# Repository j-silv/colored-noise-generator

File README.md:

# Colored Noise Generator
A white, pink, and brown noise analog signal generator.

# Schematic

# PCB

A single-layer board, DIY-fabricated at my university. Process included copper etching in vertical iron chloride (FeCl3) bath with manual agitation. Adhered to design rules (minimum trace widths, clearances, etc.) as specified by the fabrication technique.

# Simulation
*Coming soon...*

# Results
*Coming soon...*

# Acknowledgements
- Design inspired by [Rod Eliott's pink noise generator](https://sound-au.com/project11.htm)
- Thank you to Denis Muller at the [Physics and Engineering Faculty at the University of Strasbourg](https://physique-ingenierie.unistra.fr/) for helping me fabricate this board

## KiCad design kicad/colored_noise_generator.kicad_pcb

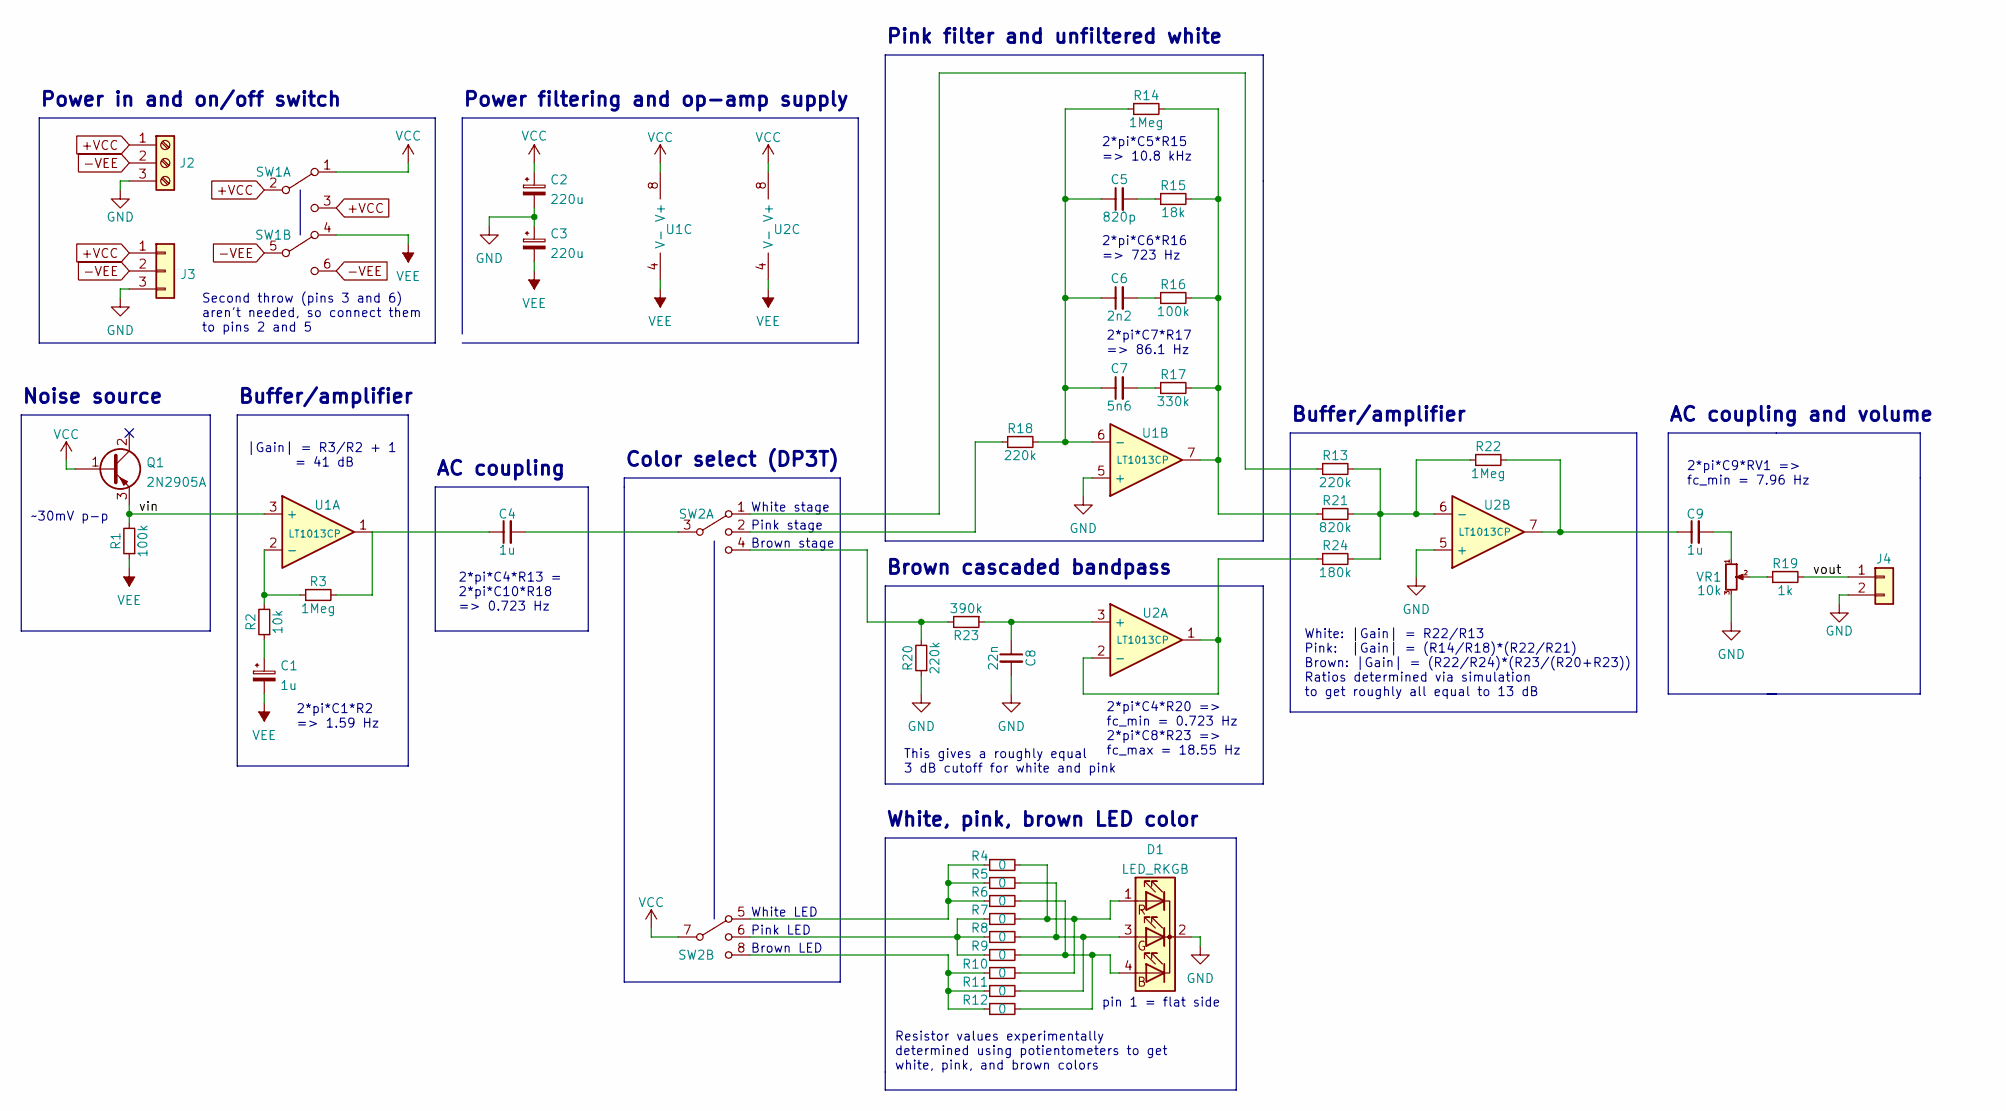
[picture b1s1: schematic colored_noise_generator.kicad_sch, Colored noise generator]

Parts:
C1: 1u; CP_Axial_L10.0mm_D6.0mm_P15.00mm_Horizontal
C2, C3: 220u; CP_Axial_L18.0mm_D8.0mm_P25.00mm_Horizontal
C4, C9: 1u; C_Rect_L7.0mm_W6.0mm_P5.00mm
C5: 820p; C_Disc_D4.7mm_W2.5mm_P5.00mm
C6: 2n2; C_Rect_L7.2mm_W2.5mm_P5.00mm_FKS2_FKP2_MKS2_MKP2
C7: 5n6; C_Rect_L7.2mm_W2.5mm_P5.00mm_FKS2_FKP2_MKS2_MKP2
C8: 22n; C_Rect_L7.2mm_W2.5mm_P5.00mm_FKS2_FKP2_MKS2_MKP2
D1: LED_RKGB; LED_D5.0mm-4_RGB
J2: Screw_Terminal_01x03; screw_terminal_1x3
J3: Conn_01x03; PinHeader_1x03_P2.54mm_Vertical
J4: Conn_01x02; PinHeader_1x02_P2.54mm_Vertical
Q1: 2N2905A; 2N2905A-TO-39
R1, R16: 100k; R_Axial_DIN0207_L6.3mm_D2.5mm_P7.62mm_Horizontal
R2: 10k; R_Axial_DIN0207_L6.3mm_D2.5mm_P7.62mm_Horizontal
R3, R14, R22: 1Meg; R_Axial_DIN0207_L6.3mm_D2.5mm_P7.62mm_Horizontal
R4, R5, R6, R7, R8, R9, R10, R11, R12: 0; R_Axial_DIN0207_L6.3mm_D2.5mm_P7.62mm_Horizontal
R13, R18, R20: 220k; R_Axial_DIN0207_L6.3mm_D2.5mm_P7.62mm_Horizontal
R15: 18k; R_Axial_DIN0207_L6.3mm_D2.5mm_P7.62mm_Horizontal
R17: 330k; R_Axial_DIN0207_L6.3mm_D2.5mm_P7.62mm_Horizontal
R19: 1k; R_Axial_DIN0207_L6.3mm_D2.5mm_P7.62mm_Horizontal
R21: 820k; R_Axial_DIN0207_L6.3mm_D2.5mm_P7.62mm_Horizontal
R23: 390k; R_Axial_DIN0207_L6.3mm_D2.5mm_P7.62mm_Horizontal
R24: 180k; R_Axial_DIN0207_L6.3mm_D2.5mm_P7.62mm_Horizontal
SW1: DPDT; dpdt
SW2: DP3T; dp3t
U1, U2: LT1013CP; DIP-8_W7.62mm_Socket
VR1: 10k; elegoo_pot

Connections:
+VCC: J2.1, J3.1, SW1.2 (B), SW1.3 (C)
-VEE: J2.2, J3.2, SW1.5 (B), SW1.6 (C)
/vin: Q1.3 (E), R1.2, U1.3 (+)
/vout: J4.1, R19.2
GND: C2.2, C3.1, C8.2, D1.2 (K), J2.3, J3.3, J4.2, R20.1, U1.5 (+), U2.5 (+), VR1.3
unnamed: C1.1, R2.1
unnamed: C4.1, R3.2, U1.1
unnamed: C4.2, SW2.3
unnamed: C5.1, C6.1, C7.1, R14.1, R18.2, U1.6 (-)
unnamed: C5.2, R15.1
unnamed: C6.2, R16.1
unnamed: C7.2, R17.1
unnamed: C8.1, R23.1, U2.3 (+)
unnamed: C9.1, R22.2, U2.7
unnamed: C9.2, VR1.1
unnamed: D1.1 (RA), R4.2, R7.2, R10.2
unnamed: D1.3 (GA), R5.2, R8.2, R11.2
unnamed: D1.4 (BA), R6.2, R9.2, R12.2
unnamed: R2.2, R3.1, U1.2 (-)
unnamed: R4.1, R5.1, R6.1, SW2.5
unnamed: R7.1, R8.1, R9.1, SW2.6
unnamed: R10.1, R11.1, R12.1, SW2.8
unnamed: R13.1, SW2.1
unnamed: R13.2, R21.2, R22.1, R24.2, U2.6 (-)
unnamed: R14.2, R15.2, R16.2, R17.2, R21.1, U1.7
unnamed: R18.1, SW2.2
unnamed: R19.1, VR1.2
unnamed: R20.2, R23.2, SW2.4
unnamed: R24.1, U2.1, U2.2 (-)
VCC: C2.1, Q1.1 (B), SW1.1 (A), SW2.7, U1.8 (V+), U2.8 (V+)
VEE: C1.2, C3.2, R1.1, SW1.4 (A), U1.4 (V-), U2.4 (V-)

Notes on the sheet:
Color select (DP3T)
~30mV p-p
2*pi*C4*R20 => fc_min = 0.723 Hz 2*pi*C8*R23 => fc_max = 18.55 Hz
Resistor values experimentally determined using potientometers to get white, pink, and brown colors
pin 1 = flat side
White, pink, brown LED color
Power in and on/off switch
Buffer/amplifier
Brown LED
2*pi*C6*R16 => 723 Hz
2*pi*C9*RV1 => fc_min = 7.96 Hz
Noise source
Pink filter and unfiltered white
Pink LED
|Gain| = R3/R2 + 1 = 41 dB
2*pi*C5*R15 => 10.8 kHz
2*pi*C7*R17 => 86.1 Hz
Pink stage
2*pi*C1*R2 => 1.59 Hz
2*pi*C4*R13 = 2*pi*C10*R18 => 0.723 Hz
White LED
Brown stage
Second throw (pins 3 and 6) aren't needed, so connect them to pins 2 and 5
White stage
White: |Gain| = R22/R13 Pink: |Gain| = (R14/R18)*(R22/R21) Brown: |Gain| = (R22/R24)*(R23/(R20+R23)) Ratios determined via simulation to get roughly all equal to 13 dB
Brown cascaded bandpass
AC coupling and volume
Power filtering and op-amp supply
AC coupling
This gives a roughly equal 3 dB cutoff for white and pink

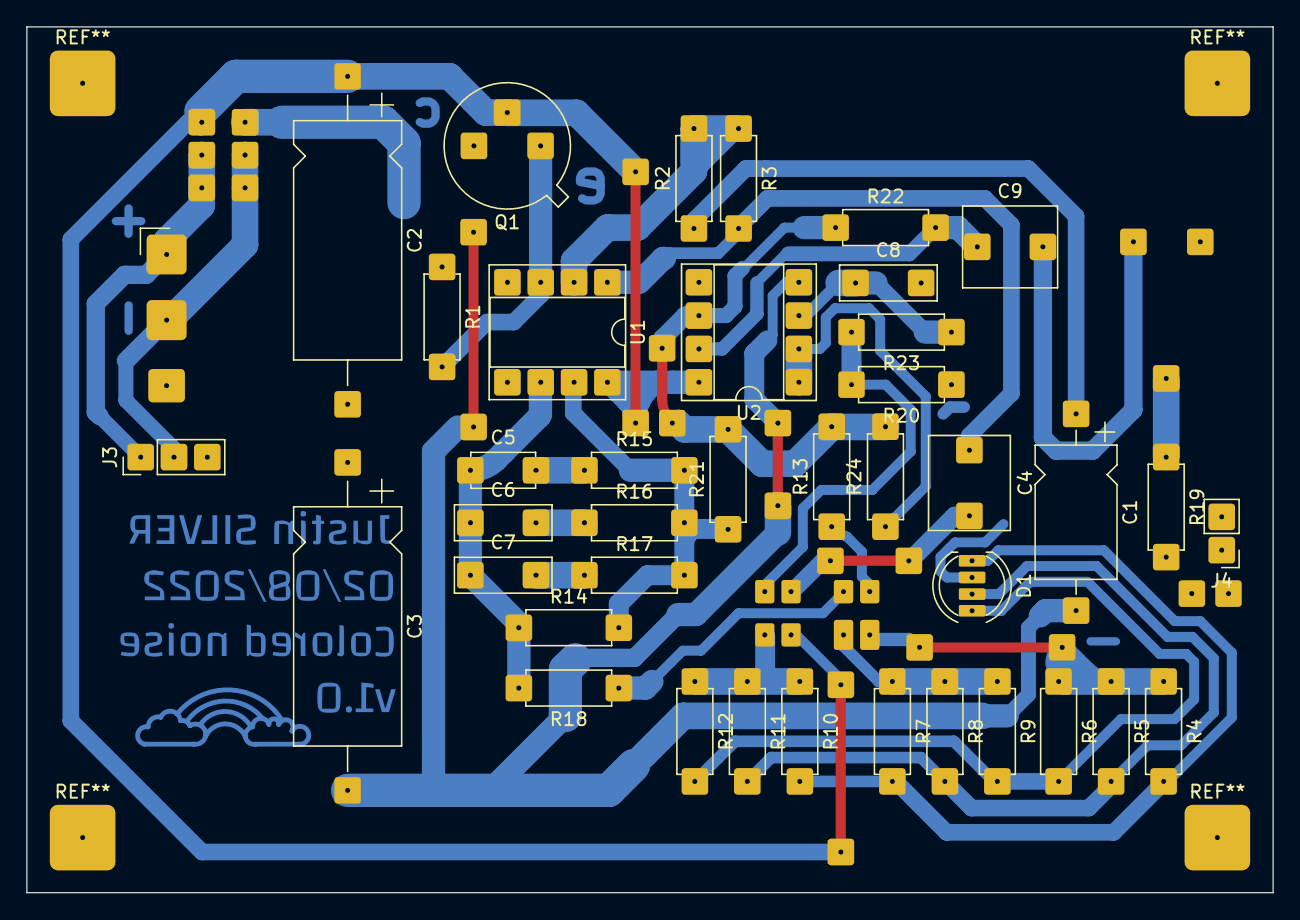
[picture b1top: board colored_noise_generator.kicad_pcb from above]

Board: 2 copper layers, 95.0 x 66.0 mm, 43 parts (0 on the bottom side), 31 nets.

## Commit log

2022-02-16 Initial commit with design files
2022-02-16 Increase pour clearance, copper pour to board edges
    Increase ground plane to trace clearance. Also add separate
    copper pour rectangles to fill to board's perimeter.
    Needed to add copper pours around graphic text with
    different clearance rules.
2022-02-19 Add photos after board fabrication
2022-03-03 Change component values while referring to simulation results
2022-08-01 Update README with images/more info and add schematic
2022-08-01 Reduce size of linked PCB images to make GitHub happy
    Apparently when linking photos via the README, there is
    a 5 MB file size limit.
2022-08-01 Remove fab outputs
    No need to include these as they can be easily regenerated from KiCad.
    Plus the files were slightly outdated.
